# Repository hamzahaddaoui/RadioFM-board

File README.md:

# Radio FM with speaker

## Abstract

In this project I developed a microcontroller based system that transmits a digital audio signal to an amplifier, attached to a speaker.
The audio signal can be received from different sources such as an FM radio module, which picks up various frequencies, or from a 3.5mm jack. Further development may include a bluetooth support.

## Details

The project began with a deep study of the TEA5767 chip, and the developing of a library for its usage.
This component is an electronically tuned FM stereo radio for low-voltage applications with fully integrated Intermediate Frequency (IF) selectivity and demodulation. The radio is completely adjustment-free and only requires a minimum of small and low cost external components. The radio can be tuned to the European, US, and Japanese FM bands.

The amplification stage was handled by the PAM8320 which is an efficient 20W mono Class-D audio power amplifier, designed to drive speakers as low as 4Ω in a bridge-tied- load configuration. Due to the low power dissipation and high efficiency of up to 95%, it can be used without any external heat sink whilst playing music.

The microcontroller mounted on the board (8-bit Microchip PIC) controls the user inputs (buttons) and  generates a response to be sent to the radio module. Using the buttons on the top of the speaker, it is possible to change frequency, save favourite stations or go on search mode.

### Schematic 

### PCB

### Board photoengraving process

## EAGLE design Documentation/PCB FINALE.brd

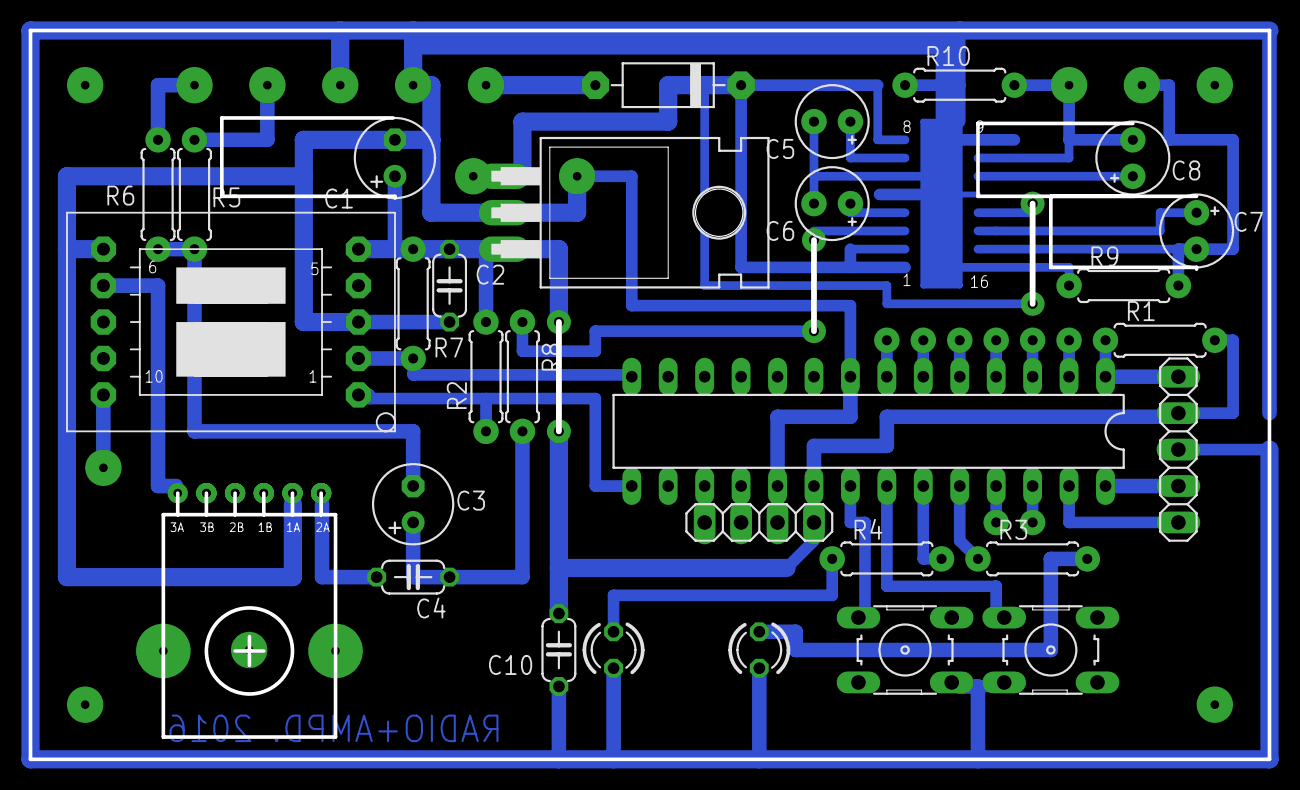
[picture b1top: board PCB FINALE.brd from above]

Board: 2 copper layers, 86.2 x 50.6 mm, 30 parts (1 on the bottom side), 18 nets.

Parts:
C1: 10u; E2,5-6
C2, C10: 100n; C050-024X044
C3: 200u; E2,5-6
C4: 1u; C050-024X044
C5, C6, C7, C8: 1u; E2,5-5
E$1: SO-16
E$3: TO220H
E$4: TEA5767
E$5: D-10
E$6: DIL28-3
E$7: 1X05
E$8: 1X04
L1, L2: LED3MM
R1, R2, R7: 10K; 0207/7
R3, R4: 330; 0207/7
R5, R6, R8: 1K; 0207/7
R9: 4k7; 0207/7
R10: 4K7; 0207/7
T1, T2: B3F-10XX

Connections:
S$7: E$6.28, E$7.2
S$8: E$6.27, E$7.1
S$9: E$4.1, E$6.15, R2.1
S$10: E$4.2, E$6.14, R7.2
S$11: C3.-, R5.1, R6.1
S$12: C3.+, C4.2, R8.2
S$21: E$6.24, R3.1
S$22: L1.A, R3.2
S$24: E$6.23, R4.2
S$25: L2.A, R4.1
S$27: C1.+, C2.1, E$3.3, E$4.5, R2.2, R7.1, R8.1
S$33: C1.-, C2.2, C10.1, E$3.2, E$4.3, E$4.6, E$6.8, E$6.19, E$7.3, E$8.3, L1.K, L2.K, R9.1, R10.1
S$49: E$6.17, E$8.1
S$50: E$6.18, E$8.2
S$51: C10.2, E$6.20, E$7.4, E$8.4, R1.2
S$54: C8.-, R10.2
S$55: E$6.1, E$7.5, R1.1
S$72: E$3.1, E$5.C
